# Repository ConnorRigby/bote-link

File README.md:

# BoteLink

Hardware design NC Miata CAN - USB passthru

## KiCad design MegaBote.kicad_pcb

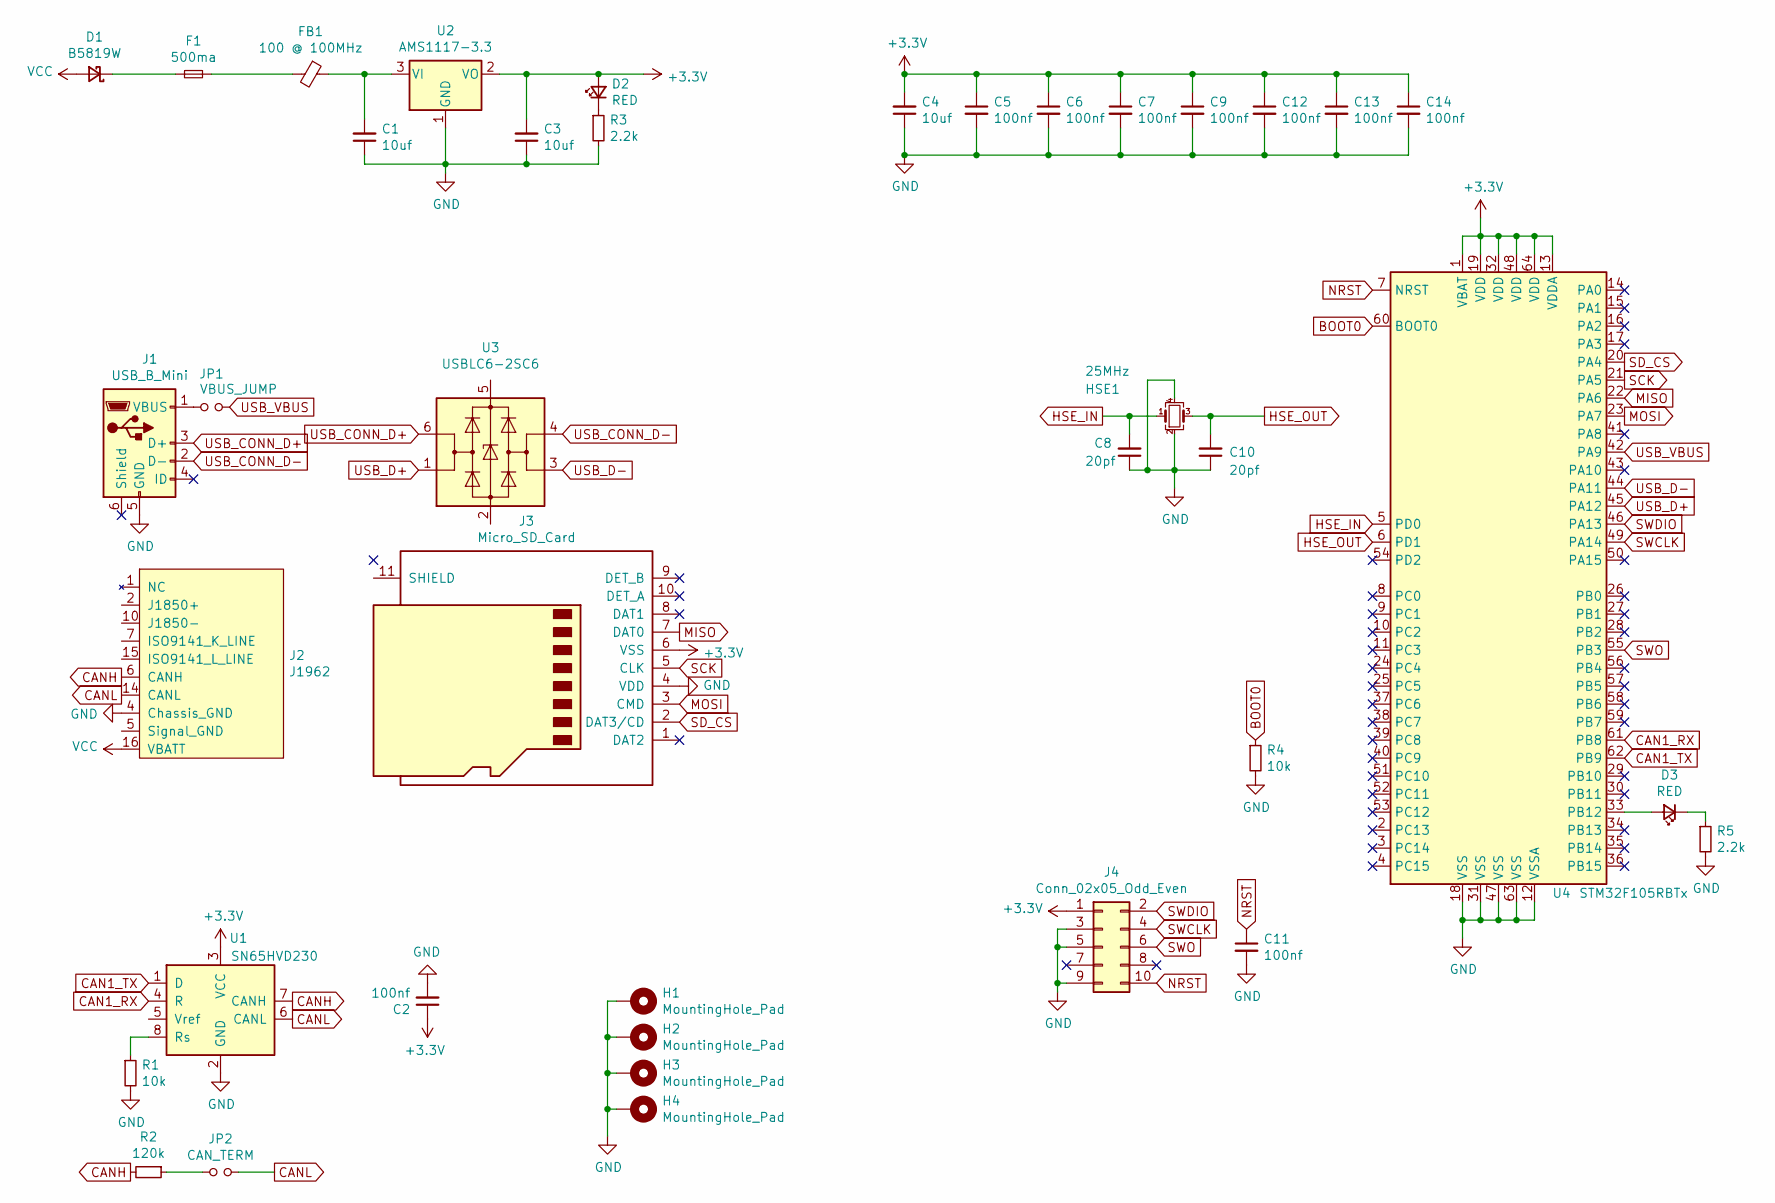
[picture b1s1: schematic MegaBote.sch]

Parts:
C1, C3, C4: 10uf; C_0805_2012Metric; LCSC_PN C15850
C2, C5, C6, C7, C9, C11, C12, C13, C14: 100nf; C_0402_1005Metric; LCSC_PN C1525
C8, C10: 20pf; C_0402_1005Metric; LCSC_PN C1554
D1: B5819W; D_SOD-123; LCSC_PN C8598
D2, D3: RED; LED_0603_1608Metric; LCSC_PN C2286
F1: 500ma; Fuse_0805_2012Metric; LCSC_PN C90129
FB1: 100 @ 100MHz; L_0805_2012Metric; LCSC_PN C1015
H1, H2, H3, H4: MountingHole_Pad; MountingHole_2.2mm_M2_Pad_Via
HSE1: 25MHz; Crystal_SMD_3225-4Pin_3.2x2.5mm; LCSC_PN C9006
J1: USB_B_Mini; USB_Mini-B_Wuerth_65100516121_Horizontal; DIGIKEY 732-2109-1-ND
J2: J1962
J3: Micro_SD_Card; microSD_HC_Molex_104031-0811; DIGIKEY WM6357CT-ND
J4: Conn_02x05_Odd_Even; PinHeader_2x05_P1.27mm_Vertical_SMD
JP1: VBUS_JUMP; PinHeader_1x02_P2.54mm_Vertical_SMD_Pin1Left
JP2: CAN_TERM; PinHeader_1x02_P2.54mm_Vertical_SMD_Pin1Left
R1, R4: 10k; R_0402_1005Metric; LCSC_PN C25744
R2: 120k; R_0402_1005Metric; LCSC_PN C25750
R3, R5: 2.2k; R_0603_1608Metric; LCSC_PN C4190
U1: SN65HVD230; SOIC-8_3.9x4.9mm_P1.27mm; LCSC_PN C12084
U2: AMS1117-3.3; SOT-223-3_TabPin2; LCSC_PN C6186
U3: USBLC6-2SC6; SOT-23-6; LCSC_PN C7519
U4: STM32F105RBTx; LQFP-64_10x10mm_P0.5mm; LCSC_PN C8349

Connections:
+3V3: C2.1, C3.2, C4.2, C5.1, C6.1, C7.1, C9.1, C12.1, C13.1, C14.1, D2.2 (A), J3.6 (VSS), J4.1, U1.3 (VCC), U2.2 (VO), U4.1 (VBAT), U4.13 (VDDA), U4.19 (VDD), U4.32 (VDD), U4.48 (VDD), U4.64 (VDD)
BOOT0: R4.1, U4.60 (BOOT0)
CAN1_RX: U1.4 (R), U4.61 (PB8)
CAN1_TX: U1.1 (D), U4.62 (PB9)
CANH: J2.6 (CANH), R2.2, U1.7 (CANH)
CANL: J2.14 (CANL), JP2.2, U1.6 (CANL)
GND: C1.1, C2.2, C3.1, C4.1, C5.2, C6.2, C7.2, C8.1, C9.2, C10.1, C11.2, C12.2, C13.2, C14.2, H1.1, H2.1, H3.1, H4.1, HSE1.2, HSE1.4, J1.5 (GND), J1.6 (Shield), J2.4 (Chassis_GND), J3.4 (VDD), J3.11 (SHIELD), J4.3, J4.5, J4.9, R1.2, R3.2, R4.2, R5.2, U1.2 (GND), U2.1 (GND), U4.12 (VSSA), U4.18 (VSS), U4.31 (VSS), U4.47 (VSS), U4.63 (VSS)
HSE_IN: C8.2, HSE1.1, U4.5 (PD0)
HSE_OUT: C10.2, HSE1.3, U4.6 (PD1)
MISO: J3.7 (DAT0), U4.22 (PA6)
MOSI: J3.3 (CMD), U4.23 (PA7)
NRST: C11.1, J4.10, U4.7 (NRST)
unnamed: C1.2, FB1.1, U2.3 (VI)
unnamed: D1.1 (K), F1.1
unnamed: D2.1 (K), R3.1
unnamed: D3.1 (K), R5.1
unnamed: D3.2 (A), U4.33 (PB12)
unnamed: F1.2, FB1.2
unnamed: J1.1 (VBUS), JP1.1
unnamed: JP2.1, R2.1
unnamed: R1.1, U1.8 (Rs)
SCK: J3.5 (CLK), U4.21 (PA5)
SD_CS: J3.2 (DAT3/CD), U4.20 (PA4)
SWCLK: J4.4, U4.49 (PA14)
SWDIO: J4.2, U4.46 (PA13)
SWO: J4.6, U4.55 (PB3)
USB_CONN_D+: J1.3 (D+), U3.6 (I/O1)
USB_CONN_D-: J1.2 (D-), U3.4 (I/O2)
USB_D+: U3.1 (I/O1), U4.45 (PA12)
USB_D-: U3.3 (I/O2), U4.44 (PA11)
USB_VBUS: JP1.2, U4.42 (PA9)
VCC: D1.2 (A), J2.16 (VBATT)

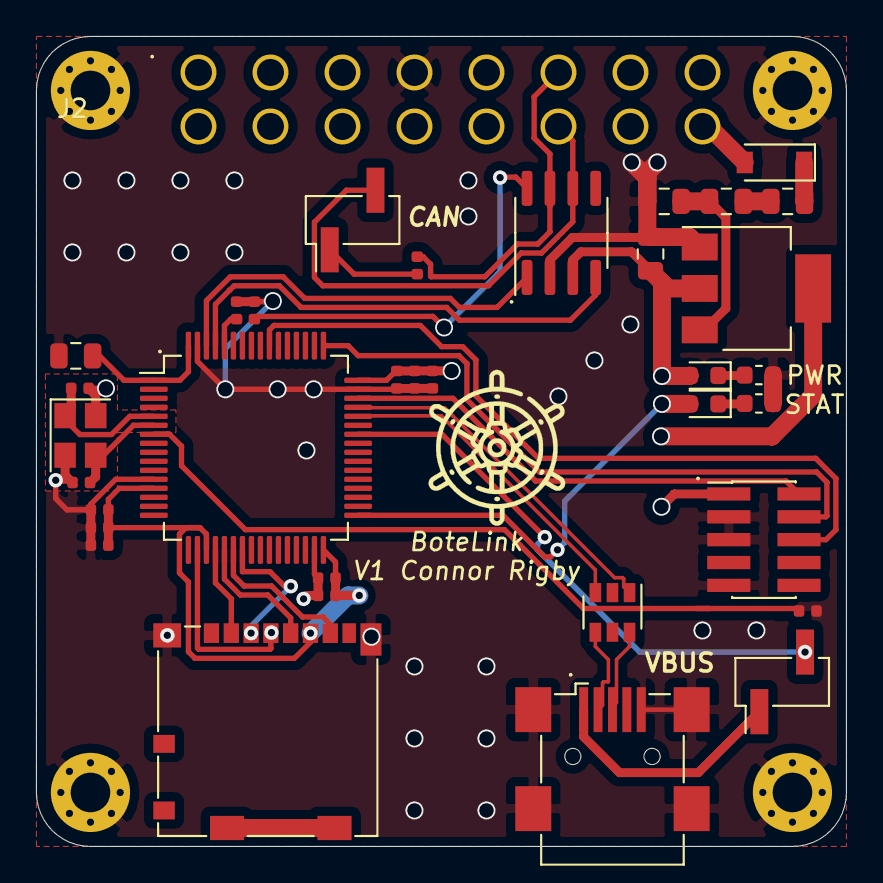
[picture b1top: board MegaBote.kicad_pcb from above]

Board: 4 copper layers, 45.0 x 45.0 mm, 39 parts (0 on the bottom side), 32 nets.

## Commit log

2020-06-27 Add screenshot
2020-07-03 Fix OBD2 footprint
2020-07-06 Address a few nits in the pcb
